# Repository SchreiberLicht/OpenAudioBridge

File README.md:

# OpenAudioBridge

OpenAudioBridge is an open hardware + firmware project aimed at replacing outdated FireWire audio interfaces in older analog mixers with modern USB audio.

The main target is the FireWire expansion card of the Mackie Onyx 1640 mixer. The goal is a direct replacement module that fits into the original slot and works without any modifications to the mixer.

---

## What this is about

A lot of older analog mixers are still perfectly usable and quiet nice to mix with, but the FireWire interfaces which added nice features like multi track recordings are either dead, unsupported or hard to replace.

This project tries to fix that by building a modern USB-based replacement that behaves like the original interface.

---

## Target (for now)

- Mackie Onyx 1640 FireWire expansion card replacement
- 18 outputs / 2 inputs (16 cannel + main R&L out + 2 in)
- internal drop-in module (no case mods, no rewiring)
- USB audio interface 

---

## Approach

The design (till now) is based on an XMOS XU316 USB audio processor with external ADC/DAC stages.

---

## Long term idea

If this works, it could become a more general platform for replacing legacy FireWire interfaces in other mixers.

But right now the focus is only the Onyx 1640.

---

## Status

Nothing is built yet.  
Right now: reverse engineering / early design phase

---

## License

Hardware: CERN-OHL-S v2  
Firmware: MIT

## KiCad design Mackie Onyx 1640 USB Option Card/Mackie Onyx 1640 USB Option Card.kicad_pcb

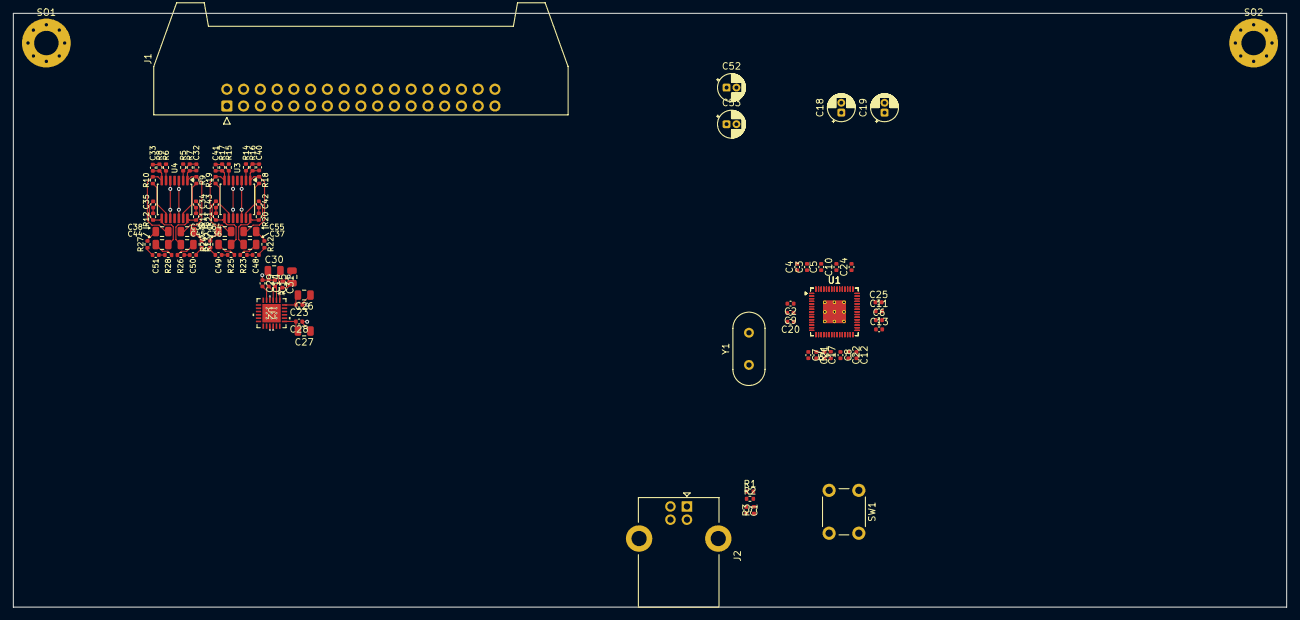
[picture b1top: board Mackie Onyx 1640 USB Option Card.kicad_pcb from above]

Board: 2 copper layers, 193.0 x 90.0 mm, 92 parts (0 on the bottom side), 56 nets.

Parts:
C1: 2u2C; C_0402_1005Metric
C2, C3, C4, C5, C6, C7, C8, C9, C10, C11, C12, C13, C15, C20, C21, C22, C23, C24, C25, C28, C31: 100nC; C_0402_1005Metric
C14, C17, C29: 1uC; C_0402_1005Metric
C16, C26, C27, C30, C36, C37, C38, C39, C44, C45, C54, C55: 10uC; C_0805_2012Metric
C18, C19, C52, C53: 10uC_Polarized; CP_Radial_D4.0mm_P1.50mm
C32, C33, C34, C35, C40, C41, C42, C43: 100pC; C_0402_1005Metric
C48, C49, C50, C51: 1n5C; C_0402_1005Metric
J1: Conn_02x17_Odd_Even; IDC-Header_2x17_P2.54mm_Latch_Horizontal
J2: USB_B; USB_B_Lumberg_2411_02_Horizontal
R1: 47kR; R_0402_1005Metric
R2: 220kR; R_0402_1005Metric
R3: 330kR; R_0402_1005Metric
R4: 600R@100Mhz; R_0402_1005Metric
R5, R6, R14, R15: 20kR; R_0402_1005Metric
R7, R8, R16, R17: 2k2R; R_0402_1005Metric
R9, R10, R11, R12, R18, R19, R20, R21: 4k7R; R_0402_1005Metric
R13, R22, R23, R24, R25, R26, R27, R28: 330R; R_0402_1005Metric
SO1, SO2: MountingHole_3.7mm_Pad_Via
SW1: SW_Push; SW_PUSH_6mm
U1, U1#2: XU316-1024-QF60B-C24; QFN-60-1EP_7x7mm_P0.4mm_EP3.4x3.4mm_ThermalVias
U2: TLV320ADC5140IRTWR; RTW24_4P15X4P15_TEX
U3, U4: LM2902; TSSOP-14_4.4x5mm_P0.65mm
Y1: 24MHz Crystal; Crystal_HC49-U_Vertical

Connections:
+5V: J1.32, J1.33, J1.34
/ADC/2CH_electronic-balancer-1/1+: C50.1, R26.2, U2.6 (IN1P_GPI1)
/ADC/2CH_electronic-balancer-1/1-: C50.2, R13.2, U2.7 (IN1M_GPO1)
/ADC/2CH_electronic-balancer-1/2+: C51.1, R28.2, U2.8 (IN2P_GPI2)
/ADC/2CH_electronic-balancer-1/2-: C51.2, R27.2, U2.9 (IN2M_GPO2)
/ADC/2CH_electronic-balancer-2/1+: C48.1, R23.2, U2.10 (IN3P_GPI3)
/ADC/2CH_electronic-balancer-2/1-: C48.2, R22.2, U2.11 (IN3M_GPO3)
/ADC/2CH_electronic-balancer-2/2+: C49.1, R25.2, U2.12 (IN4P_GPI4)
/ADC/2CH_electronic-balancer-2/2-: C49.2, R24.2, U2.13 (IN4M_GPO4)
/ADC/IN1: J1.1, R5.1
/ADC/IN2: J1.2, R6.1
/ADC/IN3: J1.3, R14.1
/ADC/IN4: J1.4, R15.1
/USB Connector/D+: J2.3 (D+), U1.29 (USB_DP), U1#2.29 (USB_DP)
/USB Connector/D-: J2.2 (D-), U1.28 (USB_DM), U1#2.28 (USB_DM)
/USB Connector/Detect: R2.2, R3.2
ADV1_AREG: C15.2, C30.2, U2.2 (AREG)
ADV1_AVDD: C9.1, C10.1, C11.1, C12.1, C16.2, C27.2, C28.2, C31.2, U1.8 (VDDIOL), U1.30 (USB_VDD33), U1.38 (VDDIOR), U1.52 (VDDIOT), U1#2.8 (VDDIOL), U1#2.30 (USB_VDD33), U1#2.38 (VDDIOR), U1#2.52 (VDDIOT), U2.1 (AVDD), U2.19 (IOVDD)
ADV1_DREG: C23.2, C26.2, U2.24 (DREG)
ADV1_MICBIAS: C29.2, U2.5 (MICBIAS)
ADV1_VREF: C14.2, U2.3 (VREF)
BAL_V+: C52.1, J1.25, J1.26, U3.4 (V+), U4.4 (V+)
BAL_V-: C53.2, J1.27, J1.28, U3.11 (V-), U4.11 (V-)
Earth: J1.29, J1.30, J1.31, J2.5 (Shield)
GND: C1.2, C2.2, C3.2, C4.2, C5.2, C6.2, C7.2, C8.2, C9.2, C10.2, C11.2, C12.2, C13.2, C14.1, C15.1, C16.1, C17.2, C18.2, C19.2, C20.2, C21.2, C22.2, C23.1, C24.2, C25.2, C26.1, C27.1, C28.1, C29.1, C30.1, C31.1, C52.2, C53.1, J1.17, J1.18, J1.21, J1.22, J2.4 (GND), R1.2, R3.1, SW1.1, U2.4 (AVSS), U2.15 (ADDR1_MISO), U2.16 (ADDR0_SCLK), U2.25 (EPAD), U3.3 (+), U3.5 (+), U3.10 (+), U3.12 (+), U4.3 (+), U4.5 (+), U4.10 (+), U4.12 (+)
MCU_PLL_AVDD: C17.1, R4.2, U1.22 (PLL_AVDD), U1#2.22 (PLL_AVDD)
MCU_USB_VDD1V8: C7.1, C8.1, C13.1, C19.1, U1.17 (VDDIOB18), U1.26 (VDDIOB18), U1.31 (USB_VDD18), U1#2.17 (VDDIOB18), U1#2.26 (VDDIOB18), U1#2.31 (USB_VDD18)
MCU_VDD1: C2.1, C3.1, C4.1, C5.1, C6.1, C18.1, C20.1, C21.1, C22.1, C24.1, C25.1, R4.1, U1.4 (VDD), U1.12 (VDD), U1.19 (VDD), U1.27 (VDD), U1.34 (VDD), U1.42 (VDD), U1.49 (VDD), U1.57 (VDD), U1.61 (VDD), U1#2.4 (VDD), U1#2.12 (VDD), U1#2.19 (VDD), U1#2.27 (VDD), U1#2.34 (VDD), U1#2.42 (VDD), U1#2.49 (VDD), U1#2.57 (VDD), U1#2.61 (VDD)
unnamed: C32.1, C54.1, R7.2, R9.1, U4.1
unnamed: C33.1, C38.1, R8.2, R10.1, U4.7
unnamed: C34.1, C36.1, R11.2, U4.14
unnamed: C35.1, C44.1, R12.2, U4.8
unnamed: C36.2, R26.1
unnamed: C37.1, C42.1, R20.2, U3.14
unnamed: C37.2, R23.1
unnamed: C38.2, R27.1
unnamed: C39.1, C41.1, R17.2, R19.1, U3.7
unnamed: C39.2, R24.1
unnamed: C40.1, C55.1, R16.2, R18.1, U3.1
unnamed: C43.1, C45.1, R21.2, U3.8
unnamed: C44.2, R28.1
unnamed: C45.2, R25.1
unnamed: C54.2, R13.1
unnamed: C55.2, R22.1
unnamed: C1.1, J2.1 (VBUS), R1.1, R2.1
unnamed: SW1.2, U1.21 (RST_N), U1#2.21 (RST_N)
unnamed: U1.16 (XIN), U1#2.16 (XIN), Y1.1
unnamed: U1.15 (XOUT), U1#2.15 (XOUT), Y1.2
unnamed: C40.2, R14.2, R16.1, U3.2 (-)
unnamed: C41.2, R15.2, R17.1, U3.6 (-)
unnamed: C43.2, R19.2, R21.1, U3.9 (-)
unnamed: C42.2, R18.2, R20.1, U3.13 (-)
unnamed: C32.2, R5.2, R7.1, U4.2 (-)
unnamed: C33.2, R6.2, R8.1, U4.6 (-)
unnamed: C35.2, R10.2, R12.1, U4.9 (-)
unnamed: C34.2, R9.2, R11.1, U4.13 (-)

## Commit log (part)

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2026-06-01 Enhance README with project details and goals
    Expanded project description and details about the OpenAudioBridge initiative, including target mixer and approach.
2026-06-01 Kicad Files for Mackie Onyx 1640 USB extention card
2026-06-01 pcb design
2026-06-05 PCB connector documentation added
